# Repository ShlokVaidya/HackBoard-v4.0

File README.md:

# HackBoard-v4.0

A custom 75% mechanical gaming keyboard featuring a Raspberry Pi Pico 2 microcontroller, VIA keyboard configurator support, and a rotary encoder for media control. This project combines elegant PCB design, modular mechanical construction, and open-source firmware for a fully customizable typing experience.

## Electronics Design

The HackBoard v4.0 uses a matrix-based keyboard design with a Raspberry Pi Pico W as the main controller. Each switch connects to the microcontroller through a matrix circuit, with individual SOD-123 diodes preventing ghosting and ensuring reliable key registration.

The circuit is optimized for minimal latency and power efficiency, with the Pico's USB connectivity enabling VIA firmware for instant key remapping without recompilation.

## PCB Design

The PCB is a carefully routed four-layer board that integrates the switch matrix, microcontroller, and rotary encoder in a compact 75% layout. Signal integrity and ground plane continuity were prioritized for minimal EMI and stable operation.

The design includes mounting points for the stabilizers, hotswap sockets for all key positions, and a dedicated encoder footprint. Via stitching around signal traces ensures proper grounding.

## Mechanical Design

### Plate Design

The plate provides structural rigidity and supports the stabilizers while maintaining compatibility with Cherry MX switches across all positions.

### Case Design

The case forms the keyboard body and houses the PCB, plate, stabilizers, and all mounting hardware. The design balances acoustics, durability, and aesthetic appeal.

## Bill of Materials

| Component Name | Qty | Price (₹) | Price ($) | Vendor |
|---------------|-----|-----------|-----------|--------|
| Raspberry Pi Pico 2 / Pico 2 W | 1 | ₹635 | $8.00 | [Robu.in](https://robu.in/) |
| Custom 75% Keyboard PCB | 1 | ₹4,692 | $52.00 | [PowerPCB](https://powerpcb.com/) |
| MX Mechanical Switches (Akko V5) | 84 | ₹2,398 | $27.00 | [StacksKB](https://stackskb.com/store/akko-v5-creamy-yellow-pro-switch-pack-of-45/) |
| Clear Screw-In Stabilizer | 4 + 1 (6.25U) | ₹1,595 | $18.00 | [StacksKB](https://stackskb.com/store/durock-clear-screw-in-stabilizers-v2/?attribute_combination=4%2B1+Set&attribute_spacebar-size=6.25U) |
| 1N4148W Diodes (SOD-123) | 84 | ₹122 | $1.50 | [Robu.in](https://robu.in/) |
| Rotary Encoder (with push button) | 1 | ₹55 | $1.00 | [Robu.in](https://robu.in/product/hongyan-ec11h-7ce15p1zd15f7-rotary-encoder-with-push-button-switch-vertical-plug-in-5-pin-360-degree/) |
| Keycap Set (75% compatible) | 1 set | ₹2,399 | $27.00 | [Robu.in](https://robu.in/) |
| M2.5 Screws | 7 | ₹43.30 | $0.50 | [OnlyScrews.in](https://onlyscrews.in/) |
| M2.5 Heat-set Inserts | 7 | ₹14.00 | $0.20 | [OnlyScrews.in](https://onlyscrews.in/) |
| M1.6 Screws | 5 | ₹16.00 | $0.20 | [OnlyScrews.in](https://onlyscrews.in/) |
| Shipping (Robu.in) | 1 | ₹49 | $0.59 | [Robu.in](https://robu.in/) |
| Shipping (OnlyScrews.in) | 1 | ₹60 | $0.72 | [OnlyScrews.in](https://onlyscrews.in/) |

---

## Total Cost

**Total (INR): ₹12,078.30**  
**Total (USD): $136.71**

## Project Files

```
PCB/
├── HackBoard v4.kicad_sch    # KiCad schematic
├── HackBoard v4.kicad_pcb    # KiCad PCB layout
├── HackBoard v4.kicad_pro    # KiCad project settings

CAD/
├── Case.step                 # Case 3D model (STEP format)
├── plate.step                # Plate 3D model (STEP format)
├── Top Cover.step            # Top cover 3D model (STEP format)

production/
├── bom.csv                   # Bill of Materials
├── designators.csv           # Component designators
├── positions.csv             # Pick-and-place coordinates
└── netlist.ipc               # IPC netlist format
```

## License

This project is licensed under the MIT License. See [LICENSE](LICENSE) for details.

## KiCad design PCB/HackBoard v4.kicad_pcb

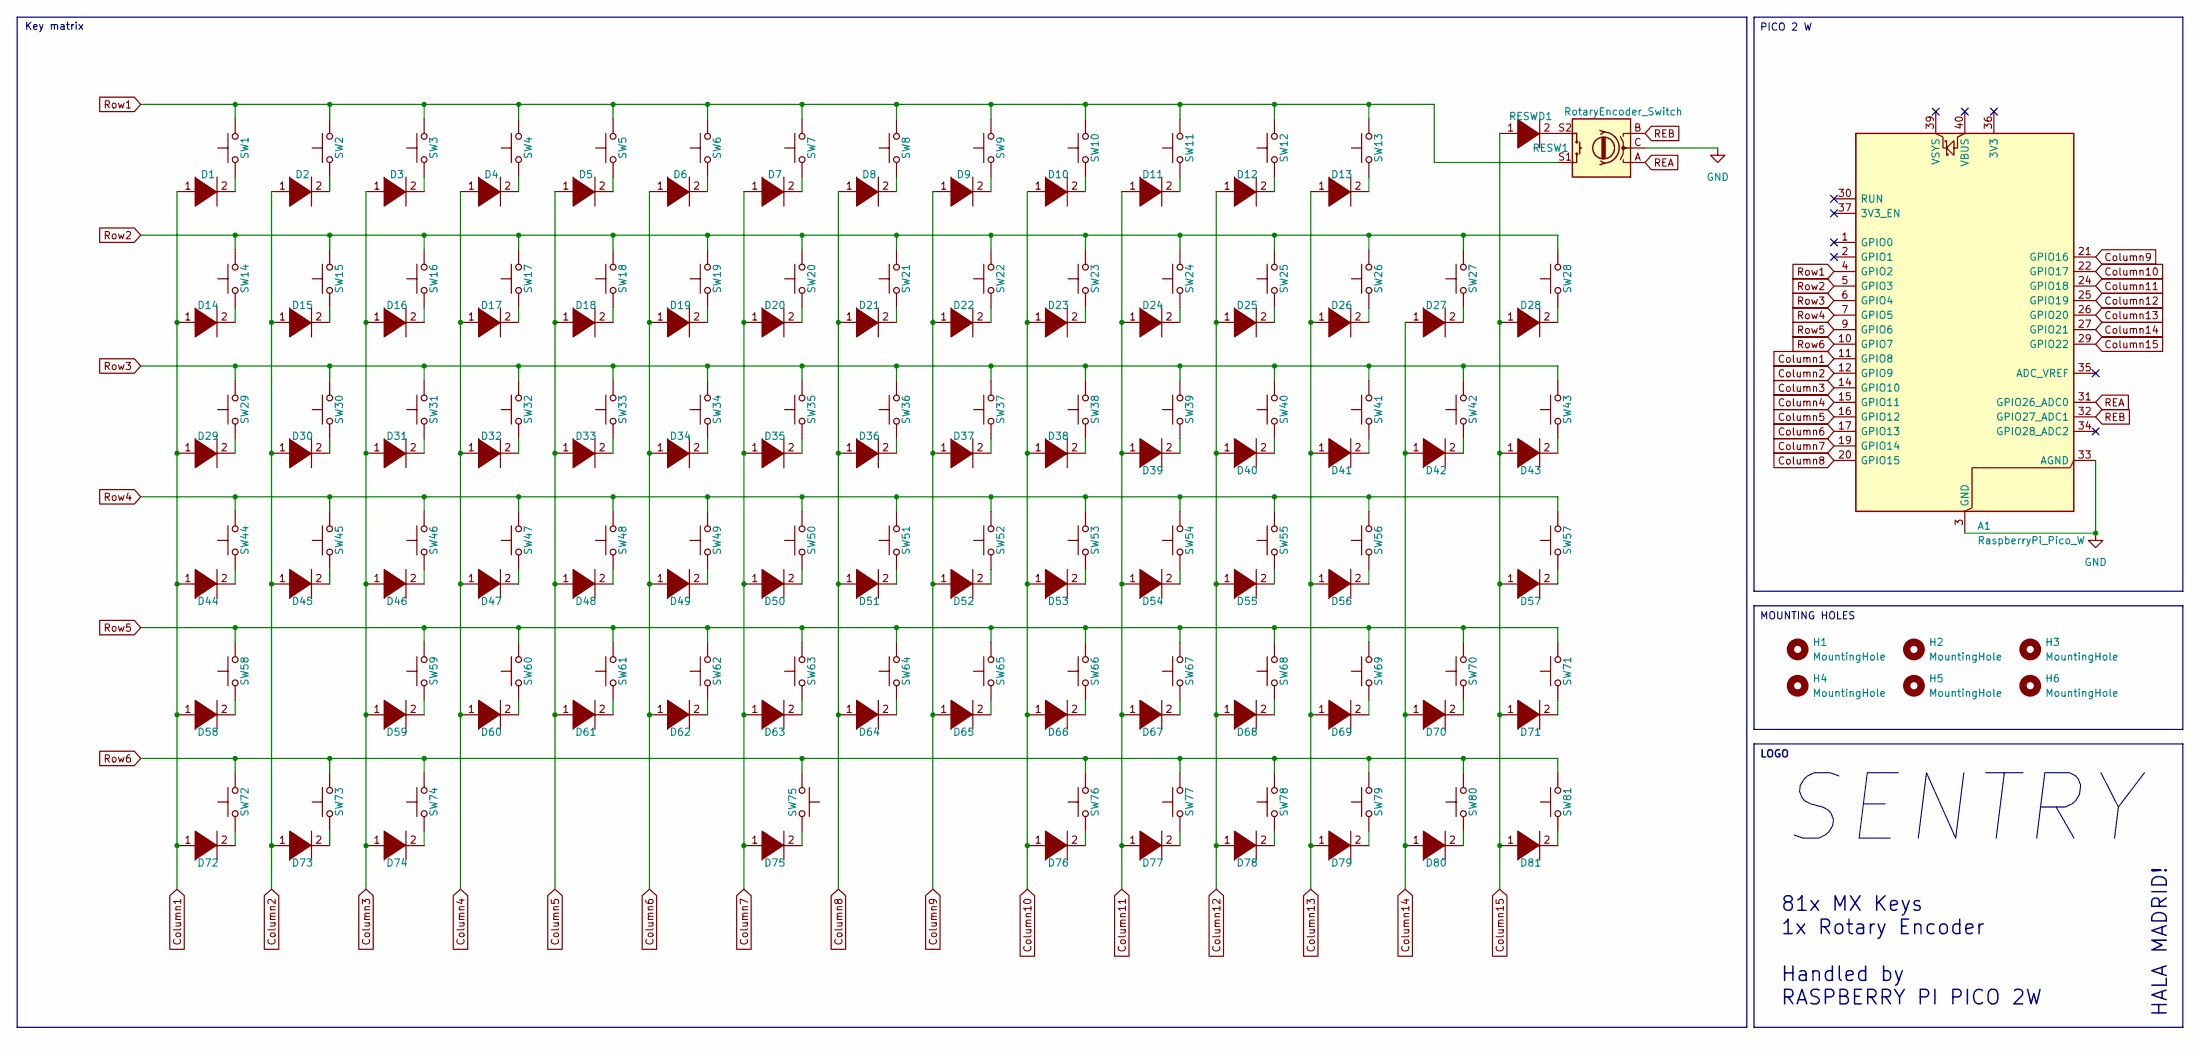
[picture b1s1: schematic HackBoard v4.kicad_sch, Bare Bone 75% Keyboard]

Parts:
A1: RaspberryPi_Pico_W; RaspberryPi_Pico_Common_THT
D1: DIODE; D_SOD-123; JLCPCB C81598
D2, D3, D4, D5, D6, D7, D8, D9, D10, D11, D12, D13, D14, D15, D16, D17, D18, D19, D20, D21, D22, D23, D24, D25, D26, D27, D28, D29, D30, D31, D32, D33, D34, D35, D36, D37, D38, D39, D40, D41, D42, D43, D44, D45, D46, D47, D48, D49, D50, D51, D52, D53, D54, D55, D56, D57, D58, D59, D60, D61, D62, D63, D64, D65, D66, D67, D68, D69, D70, D71, D72, D73, D74, D75, D76, D77, D78, D79, D80, D81: DIODE; D_SOD-123
H1, H2, H3, H4, H5, H6: MountingHole; MountingHole_2.7mm_M2.5
RESW1: RotaryEncoder_Switch; RotaryEncoder_Alps_EC11E-Switch_Vertical_H20mm_MountingHoles
RESWD1: DIODE; D_SOD-123
SW1, SW2, SW3, SW4, SW5, SW6, SW7, SW8, SW9, SW10, SW11, SW12, SW13, SW14, SW15, SW16, SW17, SW18, SW19, SW20, SW21, SW22, SW23, SW24, SW25, SW26, SW28, SW30, SW31, SW32, SW33, SW34, SW35, SW36, SW37, SW38, SW39, SW40, SW41, SW43, SW45, SW46, SW47, SW48, SW49, SW50, SW51, SW52, SW53, SW54, SW55, SW56, SW57, SW59, SW60, SW61, SW62, SW63, SW64, SW65, SW66, SW67, SW68, SW70, SW71, SW76, SW77, SW78, SW79, SW80, SW81: SW_Push; SW_Cherry_MX_1.00u_PCB
SW27, SW58: SW_Push; SW_Cherry_MX_2.00u_PCB
SW29: SW_Push; SW_Cherry_MX_1.50u_PCB
SW42: SW_Push; SW_Cherry_MX_ISOEnter_PCB
SW44: SW_Push; SW_Cherry_MX_1.75u_PCB
SW69: SW_Push; SW_Cherry_MX_2.25u_PCB
SW72, SW73, SW74: SW_Push; SW_Cherry_MX_1.25u_PCB
SW75: SW_Push; SW_Cherry_MX_6.25u_PCB

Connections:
Column1: A1.11 (GPIO8), D1.1 (K), D14.1 (K), D29.1 (K), D44.1 (K), D58.1 (K), D72.1 (K)
Column2: A1.12 (GPIO9), D2.1 (K), D15.1 (K), D30.1 (K), D45.1 (K), D73.1 (K)
Column3: A1.14 (GPIO10), D3.1 (K), D16.1 (K), D31.1 (K), D46.1 (K), D59.1 (K), D74.1 (K)
Column4: A1.15 (GPIO11), D4.1 (K), D17.1 (K), D32.1 (K), D47.1 (K), D60.1 (K)
Column5: A1.16 (GPIO12), D5.1 (K), D18.1 (K), D33.1 (K), D48.1 (K), D61.1 (K)
Column6: A1.17 (GPIO13), D6.1 (K), D19.1 (K), D34.1 (K), D49.1 (K), D62.1 (K)
Column7: A1.19 (GPIO14), D7.1 (K), D20.1 (K), D35.1 (K), D50.1 (K), D63.1 (K), D75.1 (K)
Column8: A1.20 (GPIO15), D8.1 (K), D21.1 (K), D36.1 (K), D51.1 (K), D64.1 (K)
Column9: A1.21 (GPIO16), D9.1 (K), D22.1 (K), D37.1 (K), D52.1 (K), D65.1 (K)
Column10: A1.22 (GPIO17), D10.1 (K), D23.1 (K), D38.1 (K), D53.1 (K), D66.1 (K), D76.1 (K)
Column11: A1.24 (GPIO18), D11.1 (K), D24.1 (K), D39.1 (K), D54.1 (K), D67.1 (K), D77.1 (K)
Column12: A1.25 (GPIO19), D12.1 (K), D25.1 (K), D40.1 (K), D55.1 (K), D68.1 (K), D78.1 (K)
Column13: A1.26 (GPIO20), D13.1 (K), D26.1 (K), D41.1 (K), D56.1 (K), D69.1 (K), D79.1 (K)
Column14: A1.27 (GPIO21), D27.1 (K), D42.1 (K), D70.1 (K), D80.1 (K)
Column15: A1.29 (GPIO22), D28.1 (K), D43.1 (K), D57.1 (K), D71.1 (K), D81.1 (K), RESWD1.1 (K)
GND: A1.3 (GND), A1.8 (GND), A1.13 (GND), A1.18 (GND), A1.23 (GND), A1.28 (GND), A1.33 (AGND), A1.38 (GND), RESW1.C
unnamed: D1.2 (A), SW1.1
unnamed: D2.2 (A), SW2.1
unnamed: D3.2 (A), SW3.1
unnamed: D4.2 (A), SW4.1
unnamed: D5.2 (A), SW5.1
unnamed: D6.2 (A), SW6.1
unnamed: D7.2 (A), SW7.1
unnamed: D8.2 (A), SW8.1
unnamed: D9.2 (A), SW9.1
unnamed: D10.2 (A), SW10.1
unnamed: D11.2 (A), SW11.1
unnamed: D12.2 (A), SW12.1
unnamed: D13.2 (A), SW13.1
unnamed: D14.2 (A), SW14.1
unnamed: D15.2 (A), SW15.1
unnamed: D16.2 (A), SW16.1
unnamed: D17.2 (A), SW17.1
unnamed: D18.2 (A), SW18.1
unnamed: D19.2 (A), SW19.1
unnamed: D20.2 (A), SW20.1
unnamed: D21.2 (A), SW21.1
unnamed: D22.2 (A), SW22.1
unnamed: D23.2 (A), SW23.1
unnamed: D24.2 (A), SW24.1
unnamed: D25.2 (A), SW25.1
unnamed: D26.2 (A), SW26.1
unnamed: D27.2 (A), SW27.1
unnamed: D28.2 (A), SW28.1
unnamed: D29.2 (A), SW29.1
unnamed: D30.2 (A), SW30.1
unnamed: D31.2 (A), SW31.1
unnamed: D32.2 (A), SW32.1
unnamed: D33.2 (A), SW33.1
unnamed: D34.2 (A), SW34.1
unnamed: D35.2 (A), SW35.1
unnamed: D36.2 (A), SW36.1
unnamed: D37.2 (A), SW37.1
unnamed: D38.2 (A), SW38.1
unnamed: D39.2 (A), SW39.1
unnamed: D40.2 (A), SW40.1
unnamed: D41.2 (A), SW41.1
unnamed: D42.2 (A), SW42.1
unnamed: D43.2 (A), SW43.1
unnamed: D44.2 (A), SW44.1
unnamed: D45.2 (A), SW45.1
unnamed: D46.2 (A), SW46.1
unnamed: D47.2 (A), SW47.1
unnamed: D48.2 (A), SW48.1
unnamed: D49.2 (A), SW49.1
unnamed: D50.2 (A), SW50.1
unnamed: D51.2 (A), SW51.1
unnamed: D52.2 (A), SW52.1
unnamed: D53.2 (A), SW53.1
unnamed: D54.2 (A), SW54.1
unnamed: D55.2 (A), SW55.1
unnamed: D56.2 (A), SW56.1
unnamed: D57.2 (A), SW57.1
unnamed: D58.2 (A), SW58.1
unnamed: D59.2 (A), SW59.1
unnamed: D60.2 (A), SW60.1
unnamed: D61.2 (A), SW61.1
unnamed: D62.2 (A), SW62.1
unnamed: D63.2 (A), SW63.1
unnamed: D64.2 (A), SW64.1
unnamed: D65.2 (A), SW65.1
unnamed: D66.2 (A), SW66.1
unnamed: D67.2 (A), SW67.1
unnamed: D68.2 (A), SW68.1
unnamed: D69.2 (A), SW69.1
unnamed: D70.2 (A), SW70.1
unnamed: D71.2 (A), SW71.1
unnamed: D72.2 (A), SW72.1
unnamed: D73.2 (A), SW73.1
unnamed: D74.2 (A), SW74.1
unnamed: D75.2 (A), SW75.2
unnamed: D76.2 (A), SW76.1
unnamed: D77.2 (A), SW77.1
unnamed: D78.2 (A), SW78.1
unnamed: D79.2 (A), SW79.1
unnamed: D80.2 (A), SW80.1
unnamed: D81.2 (A), SW81.1
unnamed: RESW1.S2, RESWD1.2 (A)
REA: A1.31 (GPIO26_ADC0), RESW1.A
REB: A1.32 (GPIO27_ADC1), RESW1.B
Row1: A1.4 (GPIO2), RESW1.S1, SW1.2, SW2.2, SW3.2, SW4.2, SW5.2, SW6.2, SW7.2, SW8.2, SW9.2, SW10.2, SW11.2, SW12.2, SW13.2
Row2: A1.5 (GPIO3), SW14.2, SW15.2, SW16.2, SW17.2, SW18.2, SW19.2, SW20.2, SW21.2, SW22.2, SW23.2, SW24.2, SW25.2, SW26.2, SW27.2, SW28.2
Row3: A1.6 (GPIO4), SW29.2, SW30.2, SW31.2, SW32.2, SW33.2, SW34.2, SW35.2, SW36.2, SW37.2, SW38.2, SW39.2, SW40.2, SW41.2, SW42.2, SW43.2
Row4: A1.7 (GPIO5), SW44.2, SW45.2, SW46.2, SW47.2, SW48.2, SW49.2, SW50.2, SW51.2, SW52.2, SW53.2, SW54.2, SW55.2, SW56.2, SW57.2
Row5: A1.9 (GPIO6), SW58.2, SW59.2, SW60.2, SW61.2, SW62.2, SW63.2, SW64.2, SW65.2, SW66.2, SW67.2, SW68.2, SW69.2, SW70.2, SW71.2
Row6: A1.10 (GPIO7), SW72.2, SW73.2, SW74.2, SW75.1, SW76.2, SW77.2, SW78.2, SW79.2, SW80.2, SW81.2

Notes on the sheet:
SENTRY
HALA MADRID!
Key matrix
81x MX Keys 1x Rotary Encoder Handled by RASPBERRY PI PICO 2W
PICO 2 W
MOUNTING HOLES
LOGO

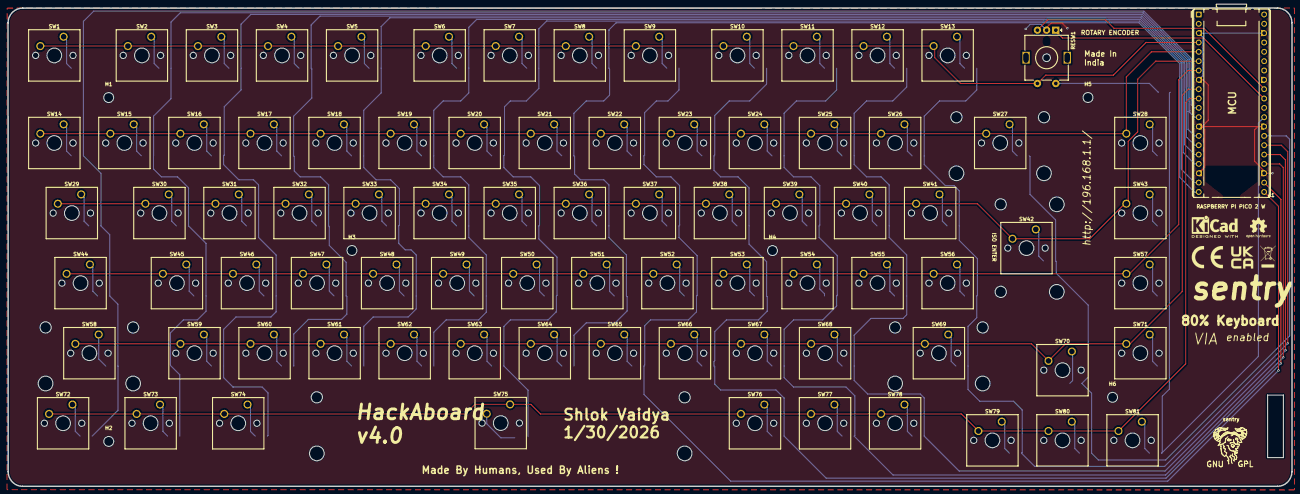
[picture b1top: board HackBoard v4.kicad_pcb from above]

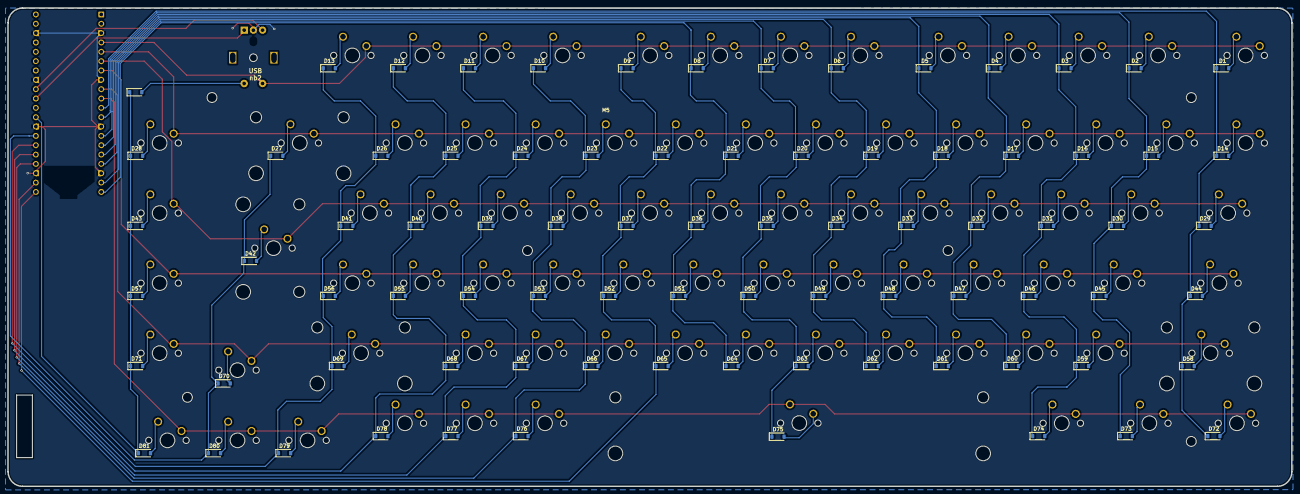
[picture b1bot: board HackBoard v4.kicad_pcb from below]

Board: 2 copper layers, 349.1 x 130.0 mm, 172 parts (82 on the bottom side), 106 nets.

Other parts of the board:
sentry: Symbol_GNU-Logo_SilkscreenTop

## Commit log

2026-02-05 Added PCB & CAD
2026-02-05 Updated the README.md
2026-02-05 Update README
    Removed features section and top cover details from README.
